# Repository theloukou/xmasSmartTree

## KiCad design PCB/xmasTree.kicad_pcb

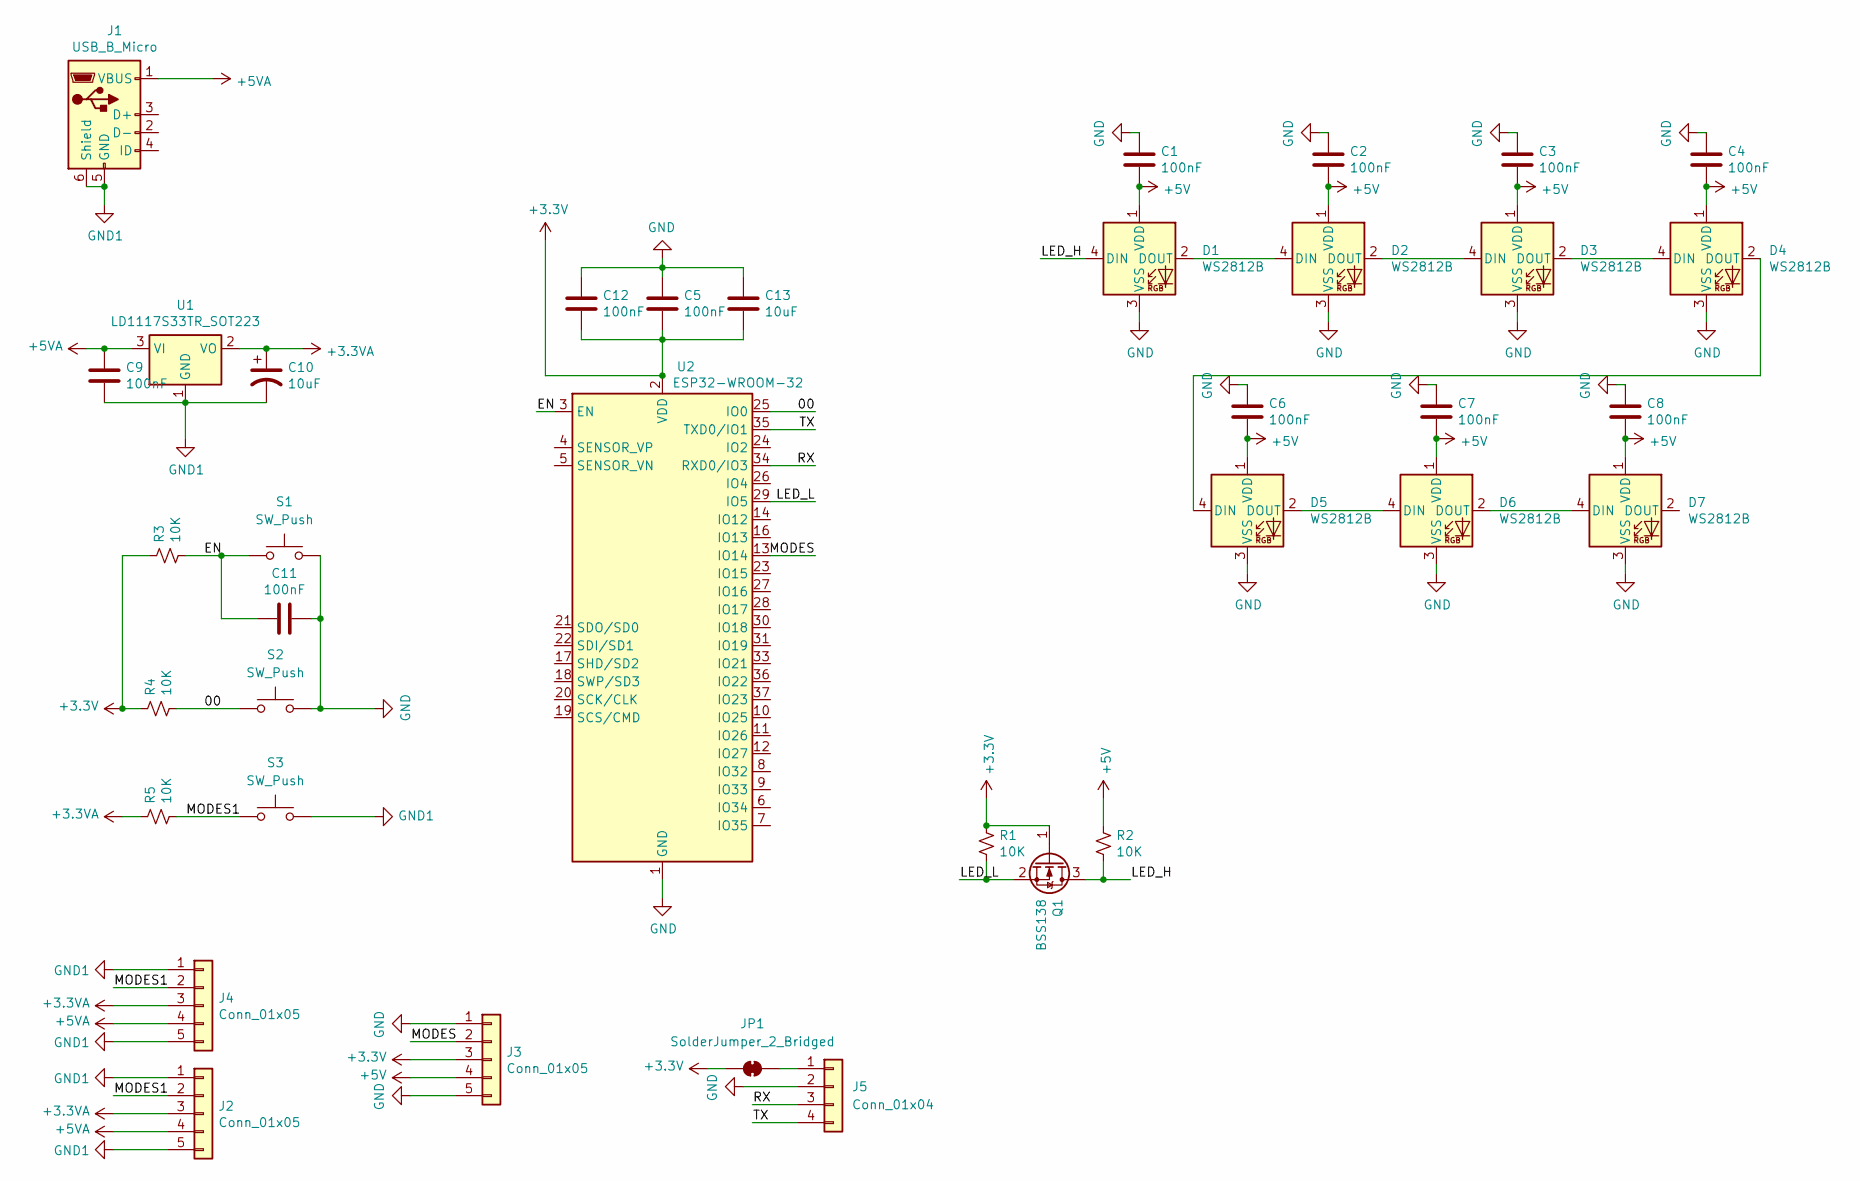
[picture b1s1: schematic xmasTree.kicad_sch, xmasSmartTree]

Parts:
C1, C2, C3, C4, C5, C6, C7, C8, C9, C11, C12: 100nF; C_0805_2012Metric_Pad1.18x1.45mm_HandSolder
C10: 10uF; CP_Radial_D10.0mm_P5.00mm_P7.50mm
C13: 10uF; C_0805_2012Metric_Pad1.18x1.45mm_HandSolder
D1, D2, D3, D4, D5, D6, D7: WS2812B; LED_WS2812B_PLCC4_5.0x5.0mm_P3.2mm
J1: USB_B_Micro; USB_Micro-B_Molex-105017-0001
J2, J3, J4: Conn_01x05; PinHeader_1x05_P2.54mm_Vertical
J5: Conn_01x04; PinSocket_1x04_P2.54mm_Horizontal
JP1: SolderJumper_2_Bridged; SolderJumper-2_P1.3mm_Bridged_Pad1.0x1.5mm
Q1: BSS138; SOT-23
R1, R2, R3, R4, R5: 10K; R_0805_2012Metric_Pad1.20x1.40mm_HandSolder
S1, S2, S3: SW_Push; SW_PUSH_1P1T_6x3.5mm_H4.3_APEM_MJTP1243
U1: LD1117S33TR_SOT223; SOT-223-3_TabPin2
U2: ESP32-WROOM-32

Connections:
+3.3V: C5.2, C12.2, C13.2, J3.3, JP1.1 (A), Q1.1 (G), R1.1, R3.1, R4.1, U2.2 (VDD)
+3.3VA: C10.1, J2.3, J4.3, R5.1, U1.2 (VO)
+5V: C1.2, C2.2, C3.2, C4.2, C6.2, C7.2, C8.2, D1.1 (VDD), D2.1 (VDD), D3.1 (VDD), D4.1 (VDD), D5.1 (VDD), D6.1 (VDD), D7.1 (VDD), J3.4, R2.1
+5VA: C9.1, J1.1 (VBUS), J2.4, J4.4, U1.3 (VI)
/00: R4.2, S2.1, U2.25 (IO0)
/EN: C11.2, R3.2, S1.1, U2.3 (EN)
/LED_H: D1.4 (DIN), Q1.3 (D), R2.2
/LED_L: Q1.2 (S), R1.2, U2.29 (IO5)
/MODES: J3.2, U2.13 (IO14)
/MODES1: J2.2, J4.2, R5.2, S3.1
/RX: J5.3, U2.34 (RXD0/IO3)
/TX: J5.4, U2.35 (TXD0/IO1)
GND: C1.1, C2.1, C3.1, C4.1, C5.1, C6.1, C7.1, C8.1, C11.1, C12.1, C13.1, D1.3 (VSS), D2.3 (VSS), D3.3 (VSS), D4.3 (VSS), D5.3 (VSS), D6.3 (VSS), D7.3 (VSS), J3.1, J3.5, J5.2, S1.2, S2.2, U2.1 (GND), U2.15 (GND), U2.38 (GND), U2.39 (GND)
GND1: C9.2, C10.2, J1.5 (GND), J1.6 (Shield), J2.1, J2.5, J4.1, J4.5, S3.2, U1.1 (GND)
unnamed: D1.2 (DOUT), D2.4 (DIN)
unnamed: D2.2 (DOUT), D3.4 (DIN)
unnamed: D3.2 (DOUT), D4.4 (DIN)
unnamed: D4.2 (DOUT), D5.4 (DIN)
unnamed: D5.2 (DOUT), D6.4 (DIN)
unnamed: D6.2 (DOUT), D7.4 (DIN)
unnamed: J5.1, JP1.2 (B)

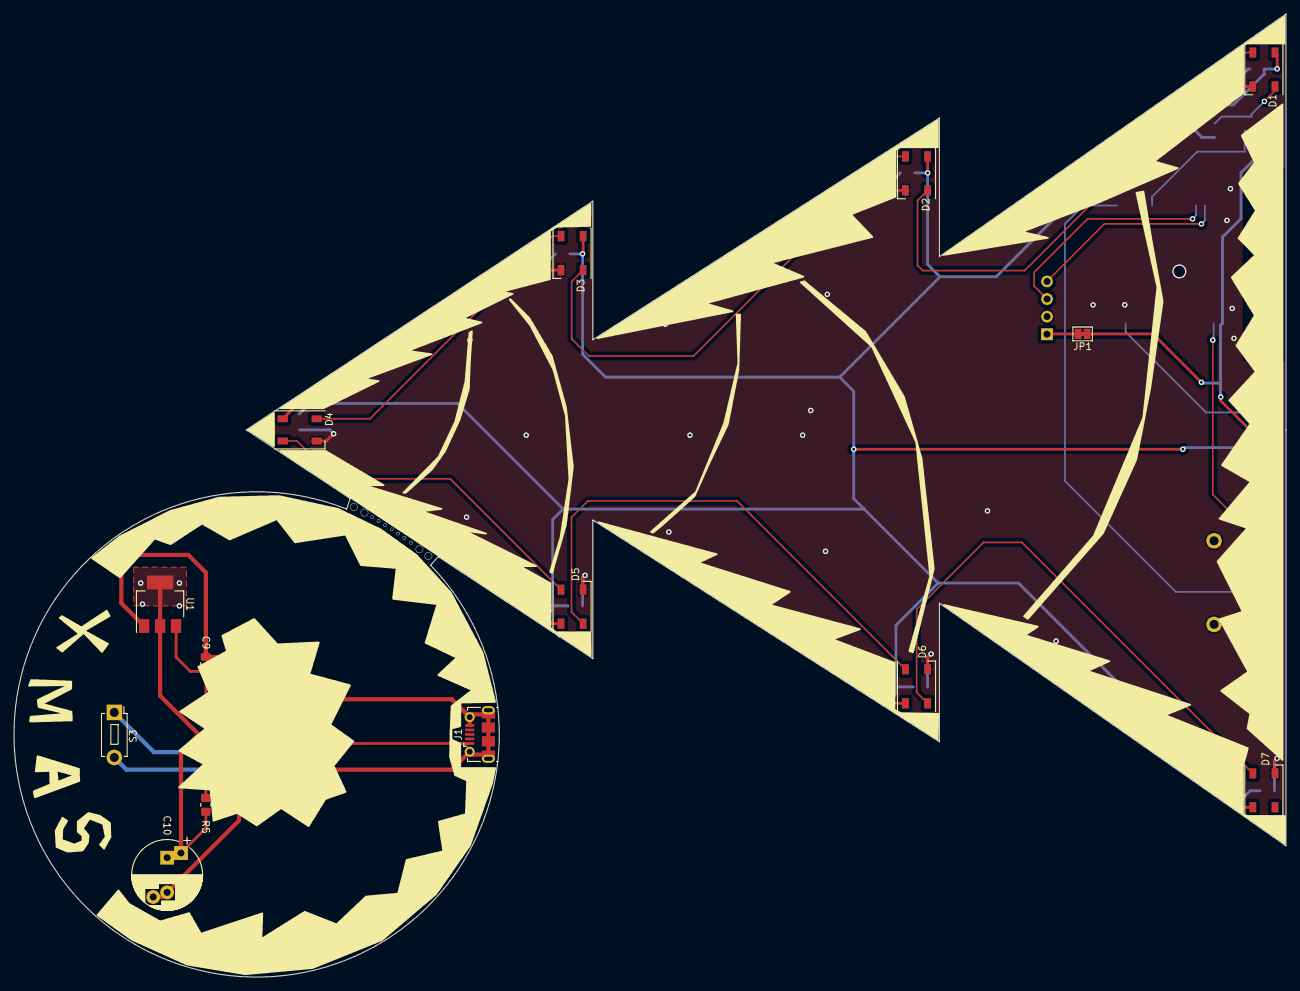
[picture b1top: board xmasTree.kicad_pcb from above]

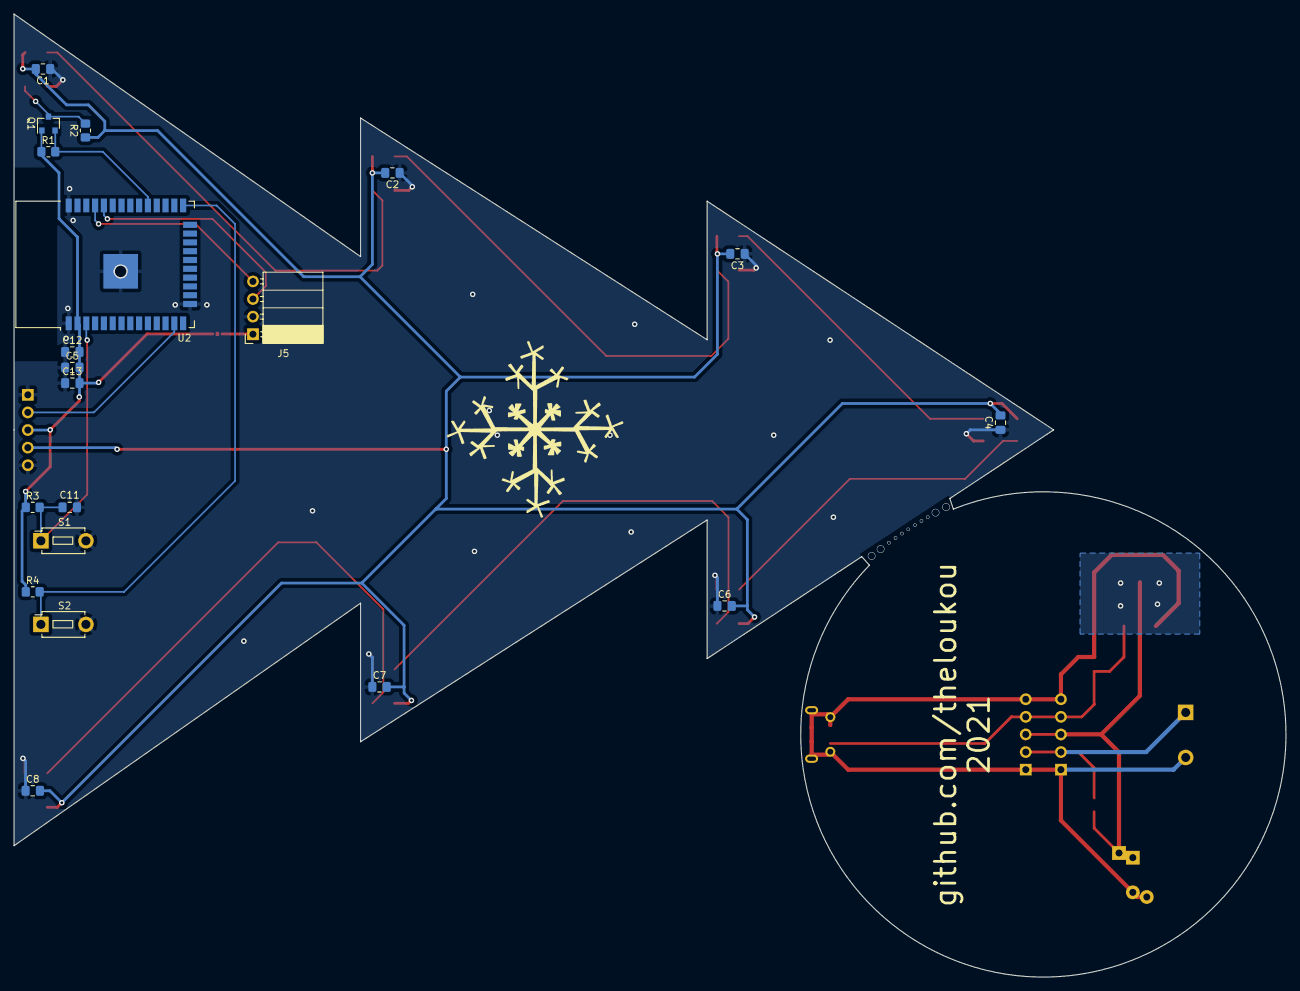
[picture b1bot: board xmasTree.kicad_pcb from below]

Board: 2 copper layers, 183.5 x 138.9 mm, 37 parts (20 on the bottom side), 21 nets.

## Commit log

2024-11-11 Initial commit Includes R1 of PCB and Fab outputs
2024-12-06 Updated to R2 4pin buttons were connected wrong. Swapped them to 2pin narrow version at the same time.
2024-12-06 Added sample ESPhome yaml Long press MODES button to turn on/off. Defaults to random twinkle effect. Double click to cycle through all effects.
